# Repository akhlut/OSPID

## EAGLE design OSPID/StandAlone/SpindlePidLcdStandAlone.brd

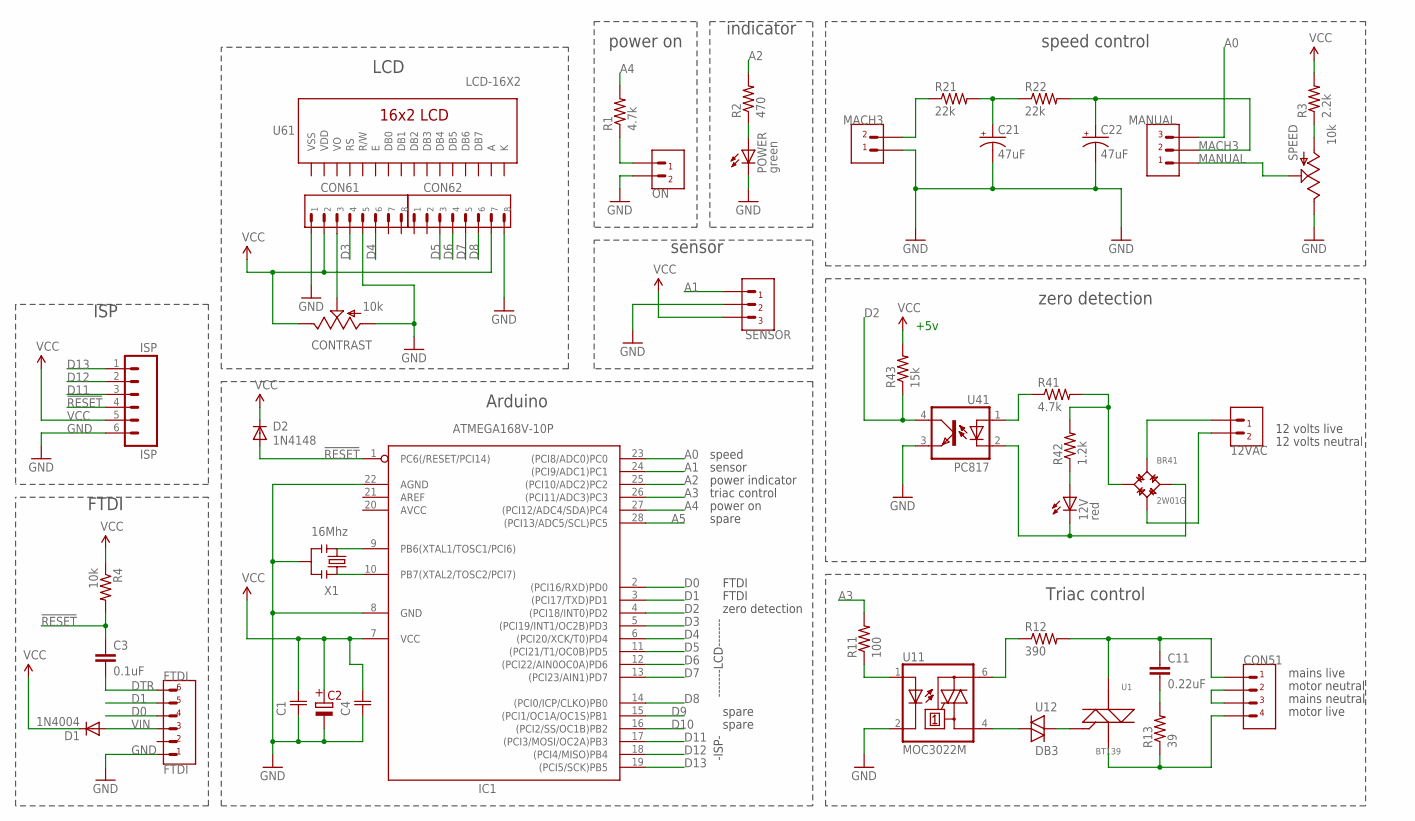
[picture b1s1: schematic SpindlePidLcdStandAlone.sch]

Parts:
12V: red; LED5MM
12VAC: 2PIN
BR41: 2W01G; DIODEBRIDGE
C1, C4: 0.1UF
C2: CAPACITOR
C3: 0.1uF; CAP-PTH-SMALL
C11: 0.22uF; CAP-PTH-SMALL
C21, C22: 47uF; CPOL-RADIAL-10UF-25V
CON51: 4PIN
CON61, CON62: 8PINHEADER
CONTRAST: 10k; ALPS_POT
D1: 1N4004; DO41-10
D2: 1N4148; DO41-10
FTDI: FTDI; 6PINHEADER
IC1: ATMEGA168V-10P; DIL28-3
ISP: ISP; 1X06
MACH3: 2PIN
MANUAL: 3PIN
ON: 2PIN
POWER: green; LED5MM
R1: 4.7k; AXIAL-0.4
R2: 470; 1/6W-RES
R3: 2.2k; 1/6W-RES
R4: 10k; AXIAL-0.4
R11: 100; 1/6W-RES
R12: 390; 1/6W-RES
R13: 39; 1/6W-RES
R21, R22: 22k; 1/6W-RES
R41: 4.7k; 1/6W-RES
R42: 1.2k; 1/6W-RES
R43: 15k; 1/6W-RES
SENSOR: 3PIN
SPEED: 10k; ALPS_POT
U1: BT139; TRIAC
U11: MOC3022M; DIL06
U12: DB3; DO35-10
U41: PC817; DIL04
U61: LCD-16X2
X1: 16Mhz; RESONATOR-PTH

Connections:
!RESET: C3.1, D2.A, IC1.1 (PC6(/RESET/PCI14)), ISP.4, R4.P$2 (2)
A: U61.15 (A)
A0: IC1.23 ((PCI8/ADC0)PC0), MANUAL.P$3 (3)
A1: IC1.24 ((PCI9/ADC1)PC1), SENSOR.P$1 (1)
A2: IC1.25 ((PCI10/ADC2)PC2), R2.2
A3: IC1.26 ((PCI11/ADC3)PC3), R11.2
A4: IC1.27 ((PCI12/ADC4/SDA)PC4), R1.P$2 (2)
A5: IC1.28 ((PCI13/ADC5/SCL)PC5)
D0: FTDI.P$4, IC1.2 ((PCI16/RXD)PD0)
D1: FTDI.P$5, IC1.3 ((PCI17/TXD)PD1)
D2: IC1.4 ((PCI18/INT0)PD2), R43.1, U41.4 (COL)
D3: CON61.P$4, IC1.5 ((PCI19/INT1/OC2B)PD3)
D4: CON61.P$6, IC1.6 ((PCI20/XCK/T0)PD4)
D5: CON62.P$3, IC1.11 ((PCI21/T1/OC0B)PD5)
D6: CON62.P$4, IC1.12 ((PCI22/AIN0OC0A)PD6)
D7: CON62.P$5, IC1.13 ((PCI23/AIN1)PD7)
D8: CON62.P$6, IC1.14 ((PCI0/ICP/CLKO)PB0)
D9: IC1.15 ((PCI1/OC1A/OC1S)PB1)
D10: IC1.16 ((PCI2/SS/OC1B)PB2)
D11: IC1.17 ((PCI3/MOSI/OC2A)PB3), ISP.3
D12: IC1.18 ((PCI4/MISO)PB4), ISP.2
D13: IC1.19 ((PCI5/SCK)PB5), ISP.1
DTR: C3.2, FTDI.P$6
GND: C1.P$1, C2.- (-VE), C4.P$1, C21.2 (-), C22.2 (-), CON61.P$1, CON61.P$5, CON62.P$8, CONTRAST.P$3 (A), FTDI.P$1, IC1.8 (GND), IC1.22 (AGND), ISP.6, MACH3.P$1, ON.P$2, POWER.K (C), SENSOR.P$2 (2), SPEED.P$1 (E), U11.2 (C), U41.3 (EMIT), X1.2
K: U61.16 (K)
MACH3: C22.1 (+), MANUAL.P$2 (2), R22.2
MACH3_PWM: MACH3.P$2, R21.1
MAINS_LIVE: C11.1, CON51.P$1, R12.2, U1.2 (A)
MANUAL: MANUAL.P$1 (1), SPEED.P$2 (S)
MOTOR_LIVE: CON51.P$4, R13.1, U1.3 (C)
unnamed: U1.1 (B), U12.C (2)
unnamed: C21.1 (+), R21.2, R22.1
unnamed: U11.4 (A1), U12.A (1)
unnamed: POWER.A, R2.1
unnamed: C11.2, R13.2
unnamed: 12V.A, R42.1
unnamed: R41.1, U41.1 (A)
unnamed: 12V.K (C), BR41.-, U41.2 (C)
unnamed: BR41.+, R41.2, R42.2
unnamed: R3.1, SPEED.P$3 (A)
unnamed: IC1.9 (PB6(XTAL1/TOSC1/PCI6)), X1.1
unnamed: ON.P$1, R1.P$1 (1)
unnamed: R11.1, U11.1 (A)
unnamed: 12VAC.P$1, BR41.AC1
unnamed: R12.1, U11.6 (A2)
unnamed: 12VAC.P$2, BR41.AC2
unnamed: CON61.P$3, CONTRAST.P$2 (S)
unnamed: IC1.10 (PB7(XTAL2/TOSC2/PCI7)), X1.3
NEUTRAL: CON51.P$2, CON51.P$3
VCC: C1.P$2, C2.+ (+VE), C4.P$2, CON61.P$2, CON62.P$7, CONTRAST.P$1 (E), D1.C, D2.C, IC1.7 (VCC), ISP.5, R3.2, R4.P$1 (1), R43.2, SENSOR.P$3 (3)
VDD: U61.2 (VDD)
VIN: D1.A, FTDI.P$3
VSS: U61.1 (VSS)

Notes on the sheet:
+5v
speed control
Arduino
sensor
power on
indicator
Triac control
zero detection
motor live
mains live
mains neutral
motor neutral
12 volts live
12 volts neutral
FTDI
ISP
LCD
-------LCD-------
-ISP-
speed
power indicator
triac control
spare

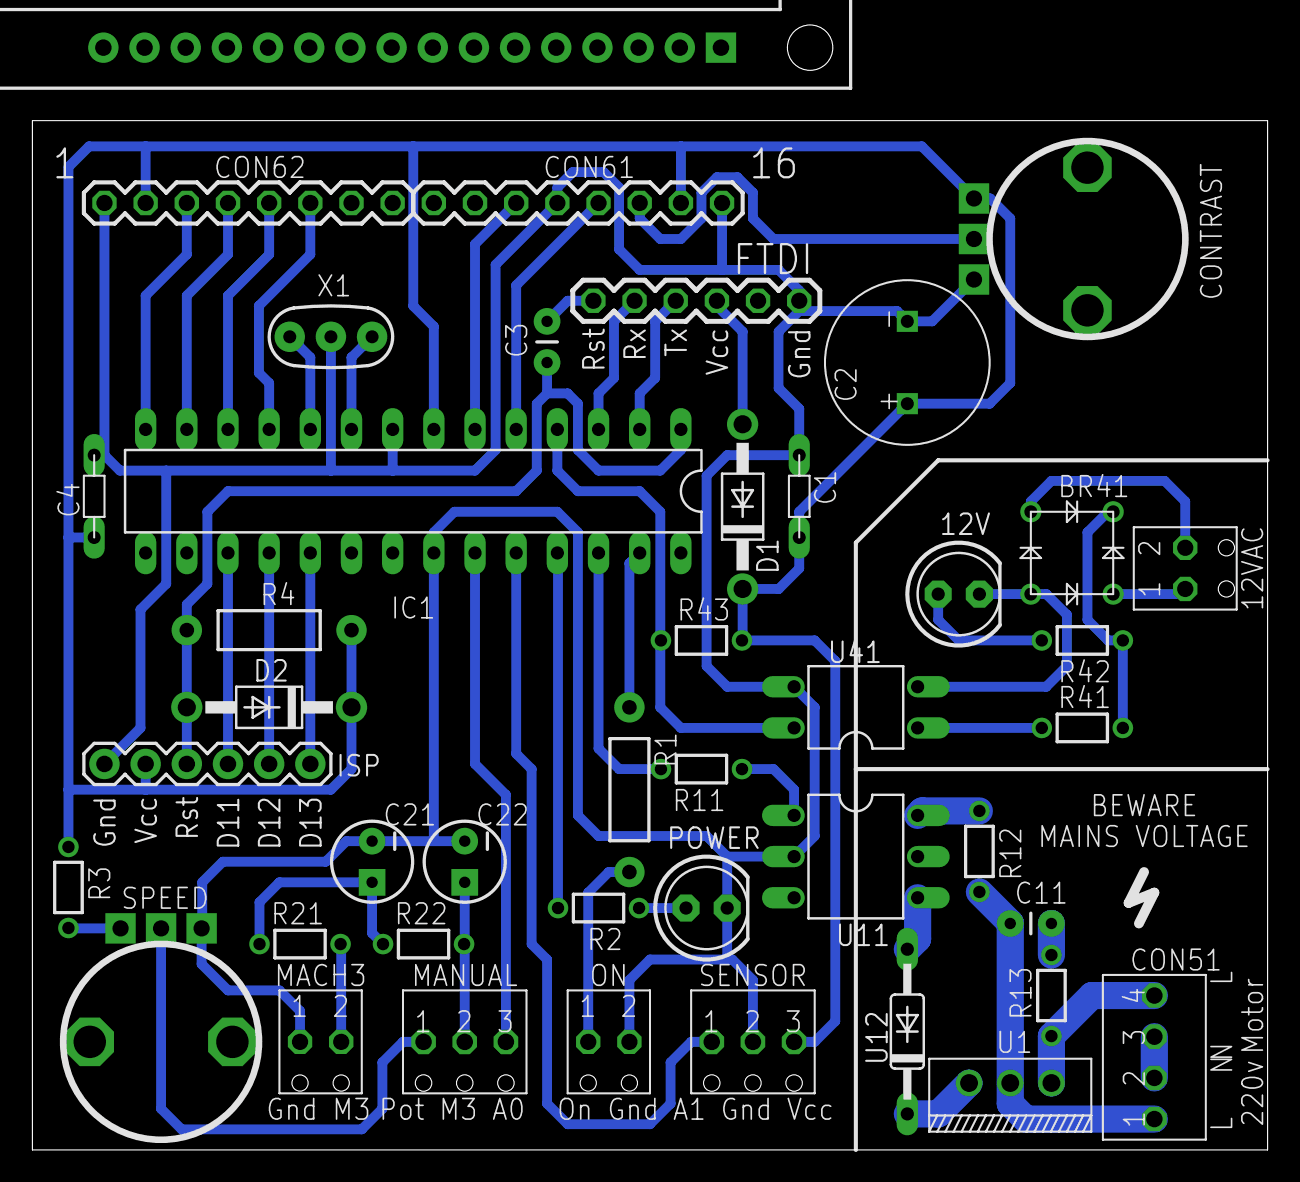
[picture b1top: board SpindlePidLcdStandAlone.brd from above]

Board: 2 copper layers, 76.2 x 63.5 mm, 43 parts (0 on the bottom side), 46 nets.

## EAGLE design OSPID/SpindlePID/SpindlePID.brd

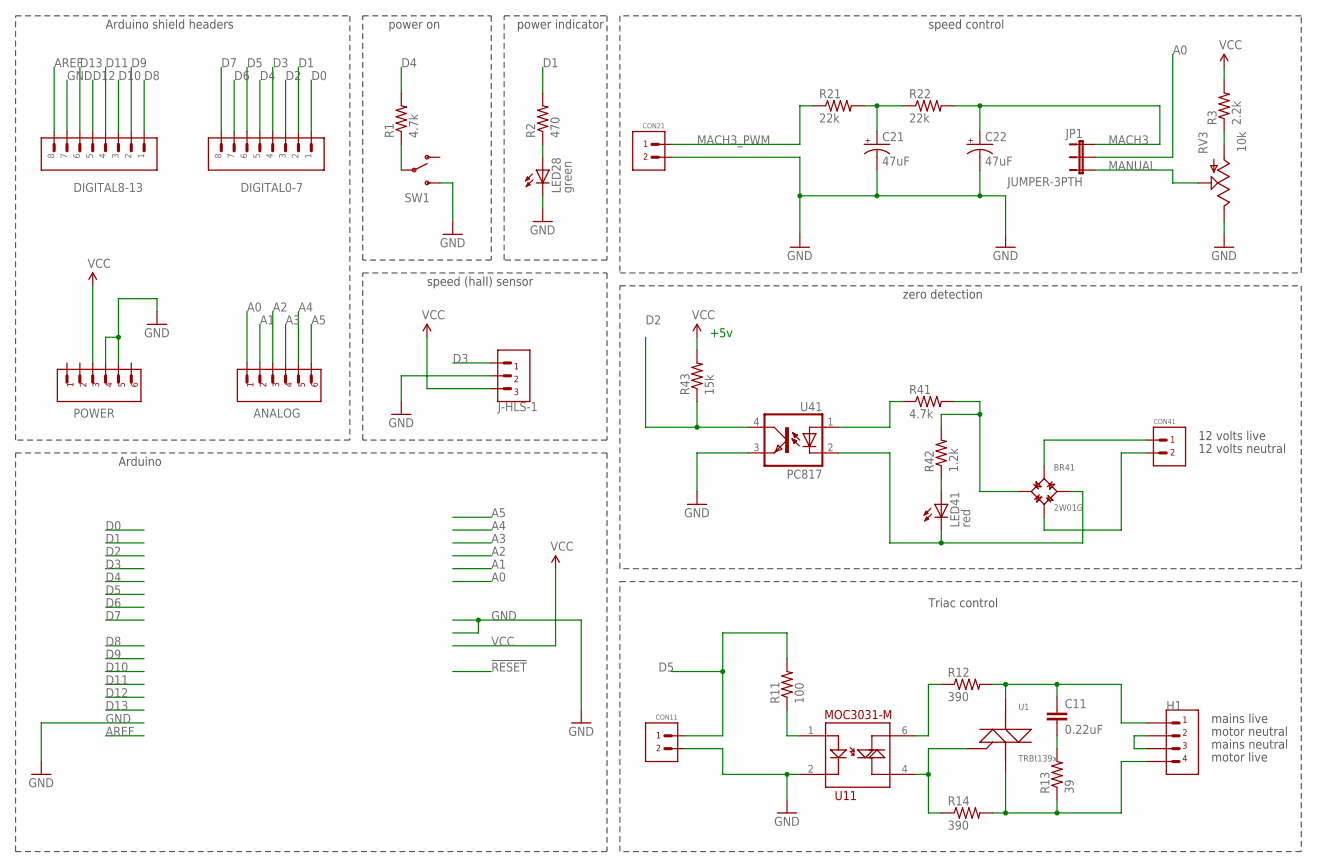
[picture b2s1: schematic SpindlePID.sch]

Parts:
ANALOG: 6PINHEADER0.1"; 6PINHEADER
BR41: 2W01G; DIODEBRIDGE
C11: 0.22uF; CAP-PTH-SMALL
C21, C22: 47uF; CPOL-RADIAL-10UF-25V
CON11, CON21, CON41: 2PINHEADER
DIGITAL0-7, DIGITAL8-13: 8PINHEADER
H1: 4PIN
J-HLS-1: 3PINHEADER
JP1: JUMPER-3PTH; 1X03
LED28: green; LED5MM
LED41: red; LED5MM
POWER: 6PINHEADER0.1"; 6PINHEADER
R1, R41: 4.7k; 1/6W-RES
R2: 470; 1/6W-RES
R3: 2.2k; 1/6W-RES
R11: 100; 1/6W-RES
R12, R14: 390; 1/6W-RES
R13: 39; 1/6W-RES
R21, R22: 22k; 1/6W-RES
R42: 1.2k; 1/6W-RES
R43: 15k; 1/6W-RES
RV3: 10k; TRIM_POT
SW1: SWITCH-SPSTPTH; SWITCH-SPDT
U1: TRBt139x; TRIAC
U11: MOC3031-M; DIL06
U41: PC817; DIL04

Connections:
A0: ANALOG.P$1, JP1.2
A1: ANALOG.P$2
A2: ANALOG.P$3
A3: ANALOG.P$4
A4: ANALOG.P$5
A5: ANALOG.P$6
AREF: DIGITAL8-13.P$8
D0: DIGITAL0-7.P$1
D1: DIGITAL0-7.P$2, R2.2
D2: DIGITAL0-7.P$3, R43.1, U41.4 (COL)
D3: DIGITAL0-7.P$4, J-HLS-1.P$3
D4: DIGITAL0-7.P$5, R1.2
D5: CON11.P$1, DIGITAL0-7.P$6, R11.2
D6: DIGITAL0-7.P$7
D7: DIGITAL0-7.P$8
D8: DIGITAL8-13.P$1
D9: DIGITAL8-13.P$2
D10: DIGITAL8-13.P$3
D11: DIGITAL8-13.P$4
D12: DIGITAL8-13.P$5
D13: DIGITAL8-13.P$6
GND: C21.2 (-), C22.2 (-), CON11.P$2, CON21.P$2, DIGITAL8-13.P$7, J-HLS-1.P$2, LED28.K (C), POWER.P$4, POWER.P$5, RV3.2 (E), SW1.3 (S), U11.2, U41.3 (EMIT)
MACH3: C22.1 (+), JP1.1, R22.2
MACH3_PWM: CON21.P$1, R21.1
MAINS_LIVE: C11.1, H1.P$1, R12.2, U1.2 (A)
MANUAL: JP1.3, RV3.1 (S)
MOTOR_LIVE: H1.P$4, R13.1, R14.2, U1.3 (C)
unnamed: C21.1 (+), R21.2, R22.1
unnamed: R14.1, U1.1 (B), U11.4
unnamed: LED28.A, R2.1
unnamed: C11.2, R13.2
unnamed: LED41.A, R42.1
unnamed: R41.1, U41.1 (A)
unnamed: BR41.-, LED41.K (C), U41.2 (C)
unnamed: BR41.+, R41.2, R42.2
unnamed: R3.1, RV3.3 (A)
unnamed: R1.1, SW1.2
unnamed: R11.1, U11.1
unnamed: BR41.AC1, CON41.P$1
unnamed: R12.1, U11.6
unnamed: BR41.AC2, CON41.P$2
NEUTRAL: H1.P$2, H1.P$3
VCC: J-HLS-1.P$1, POWER.P$3, R3.2, R43.2

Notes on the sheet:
+5v
speed control
Arduino shield headers
Arduino
speed (hall) sensor
power on
power indicator
Triac control
zero detection
motor live
mains live
mains neutral
motor neutral
12 volts live
12 volts neutral

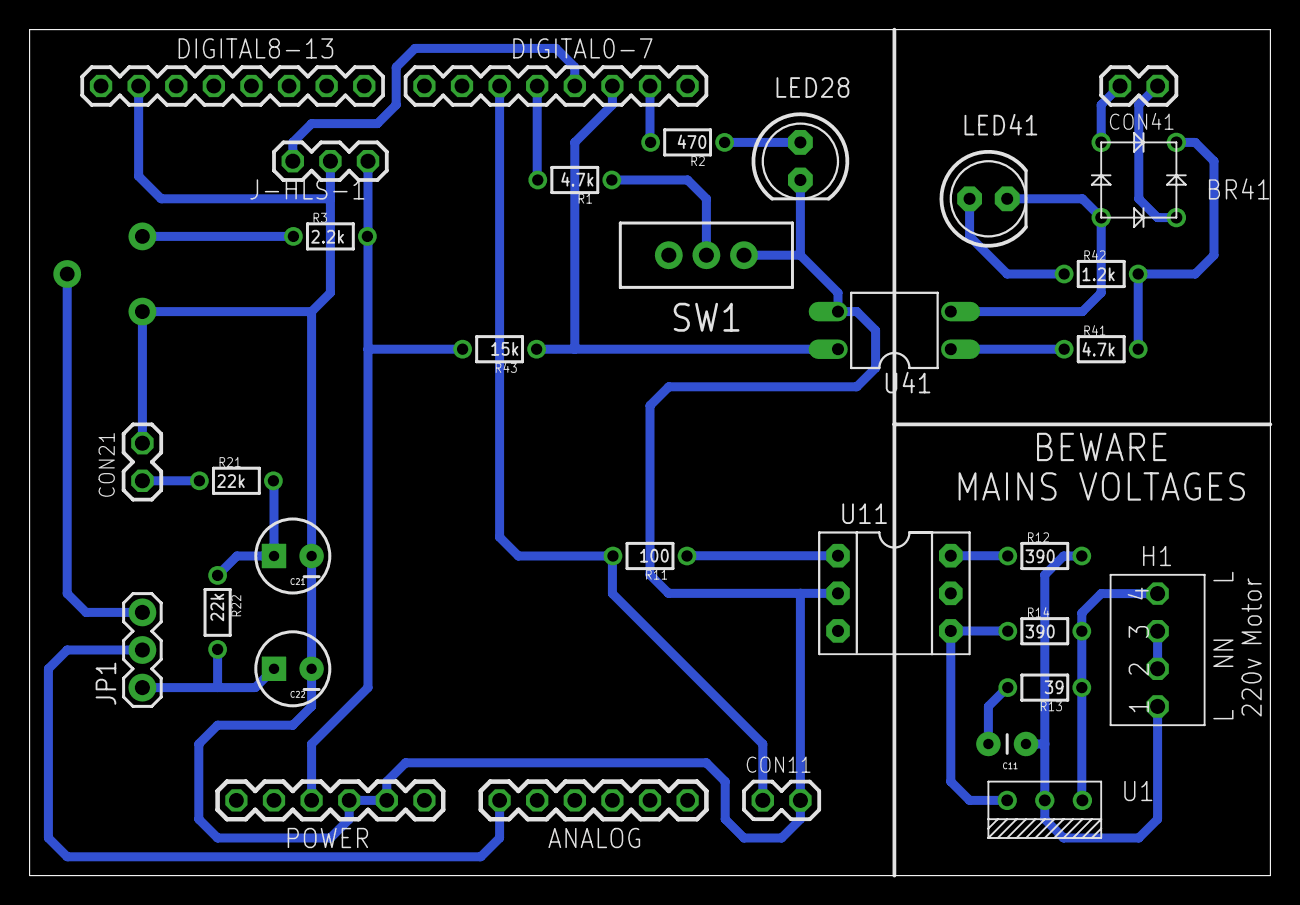
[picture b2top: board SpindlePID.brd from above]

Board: 2 copper layers, 83.8 x 57.1 mm, 33 parts (0 on the bottom side), 28 nets.

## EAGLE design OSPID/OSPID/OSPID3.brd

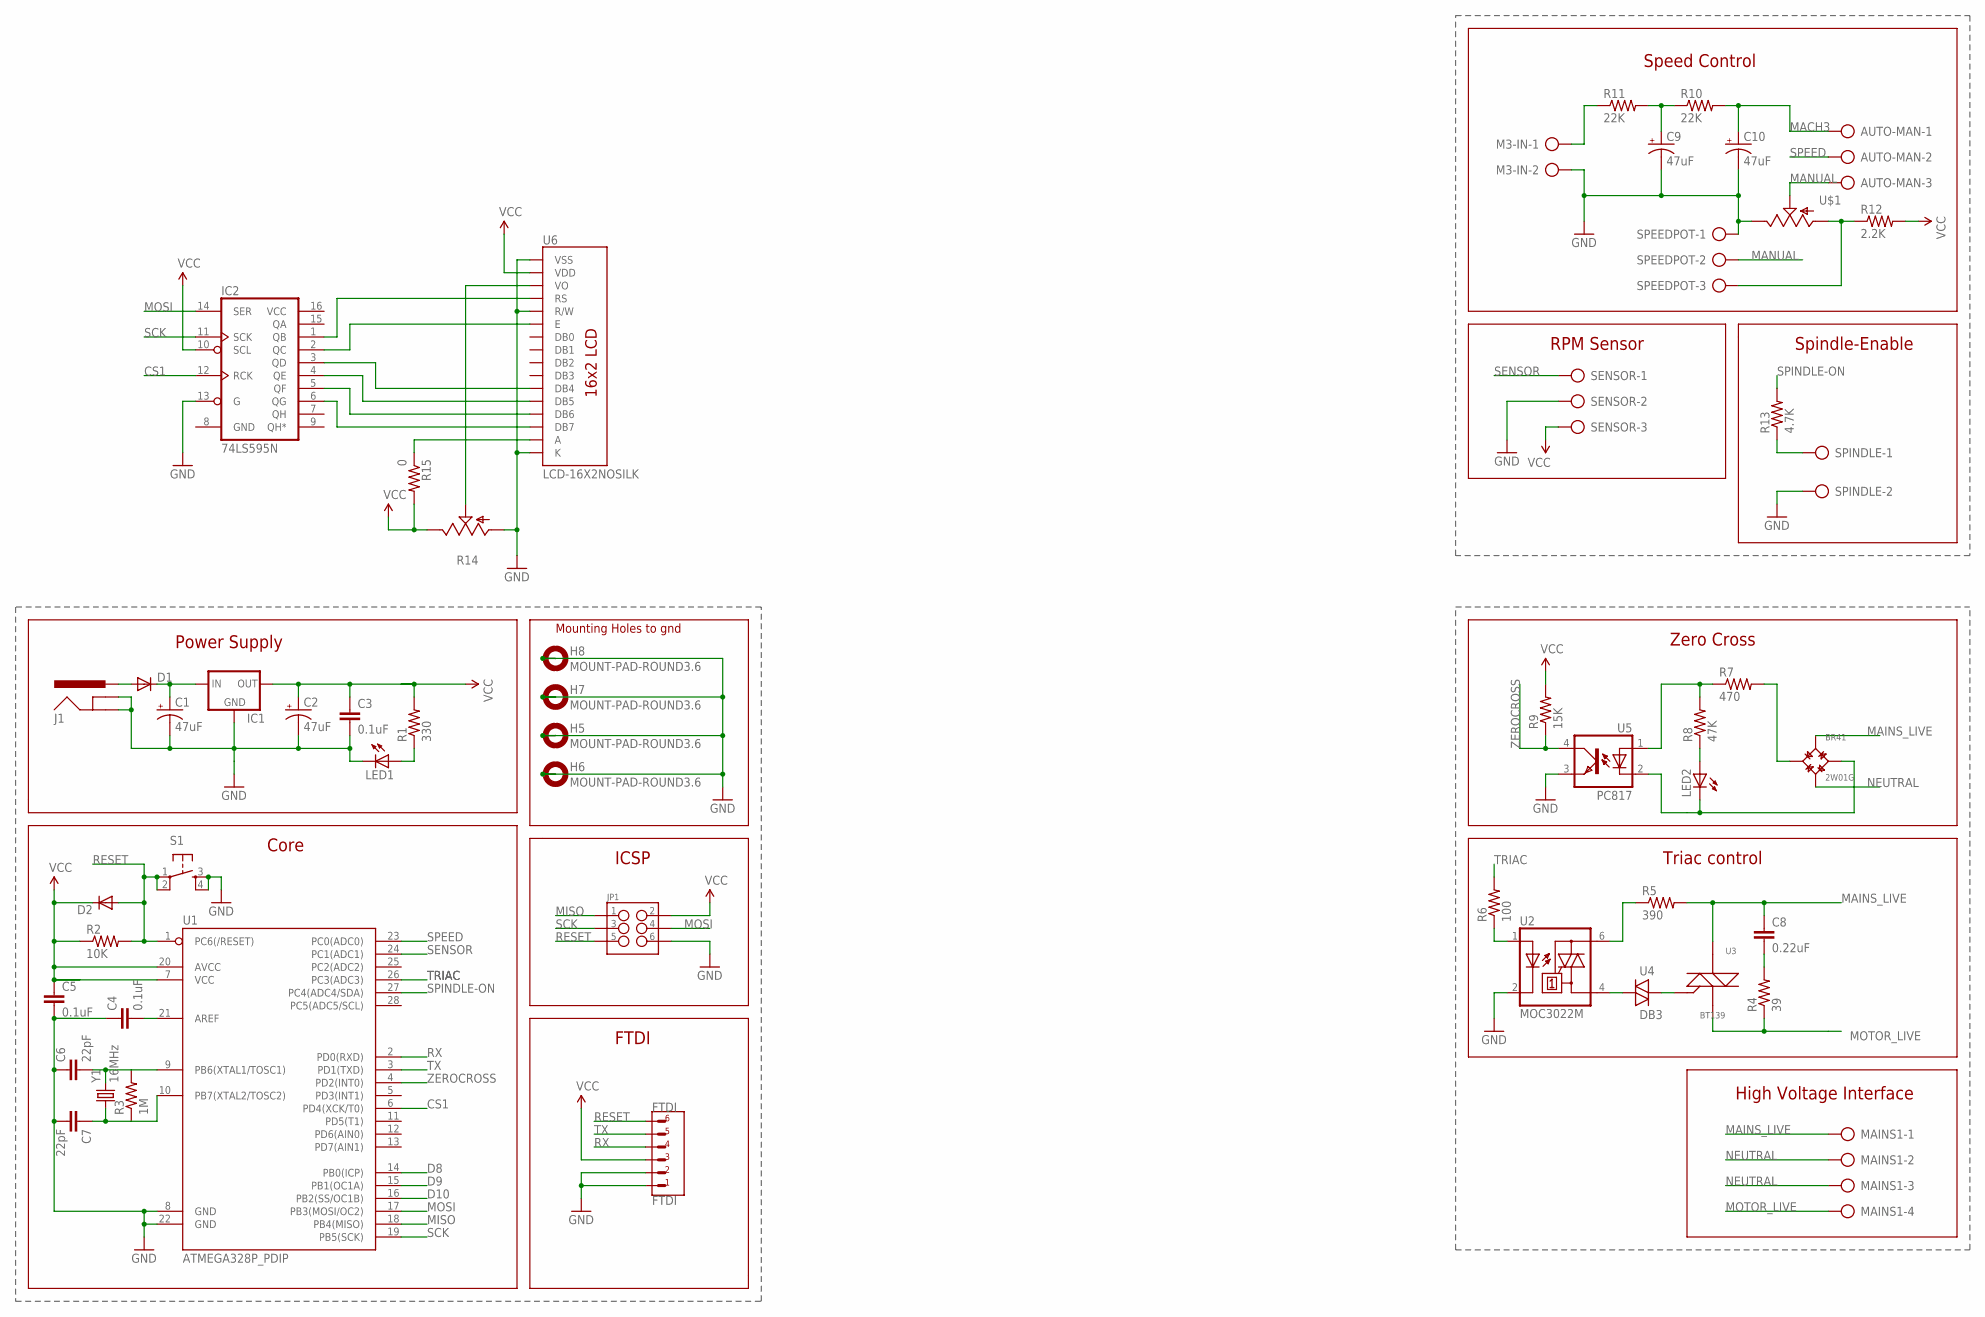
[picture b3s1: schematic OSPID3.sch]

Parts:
AUTO-MAN: AK500/3
BR41: 2W01G; DIODEBRIDGE
C1, C2, C9, C10: 47uF; CPOL-RADIAL-10UF-25V
C3, C4, C5: 0.1uF; CAP-PTH-SMALL
C6, C7: 22pF; CAP-PTH-SMALL
C8: 0.22uF; CAP-PTH-SMALL
D1, D2: DIODEPTH; DIODE-1N4001
FTDI: FTDI; 6PINHEADER
H5, H6, H7, H8: MOUNT-PAD-ROUND3.6; 3,6-PAD
IC1: V_REG_78XX-TO-220; TO-220-ALT
IC2: 74LS595N; DIL16
J1: POWER_JACKPTH_LOCK; POWER_JACK_PTH_LOCK
JP1: M03X2POGO_PINS; 2X3_POGO
LED1, LED2: LED5MM
M3-IN: AK500/2
MAINS1: AK500/4
R1: 330; AXIAL-0.3
R2: 10K; AXIAL-0.3
R3: 1M; AXIAL-0.3
R4: 39; AXIAL-0.3
R5: 390; AXIAL-0.3
R6: 100; AXIAL-0.3
R7: 470; SQM_5-10
R8: 47K; SQM_5-10
R9: 15K; AXIAL-0.3
R10, R11: 22K; AXIAL-0.3
R12: 2.2K; AXIAL-0.3
R13: 4.7K; AXIAL-0.3
R14: POT_TRIM_US-B25U; POT_B25U
R15: 0; AXIAL-0.3
S1: TAC_SWITCHPTH; TACTILE-PTH
SENSOR: AK500/3
SPEEDPOT: AK500/3
SPINDLE: AK500/2
U1: ATMEGA328P_PDIP; DIL28-3
U2: MOC3022M; DIL06
U3: BT139; TRIAC
U4: DB3; DO35-10
U5: PC817; DIL04
U6: LCD-16X2NOSILK; LCD-16X2_NOSILK
U$1: POT; ALPS_POT
Y1: 16MHz; HC49U-V

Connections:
CS1: IC2.12 (RCK), U1.6 (PD4(XCK/T0))
D8: U1.14 (PB0(ICP))
D9: U1.15 (PB1(OC1A))
D10: U1.16 (PB2(SS/OC1B))
GND: C1.2 (-), C2.2 (-), C3.2, C4.1, C5.2, C6.1, C7.2, C9.2 (-), C10.2 (-), FTDI.P$1, FTDI.P$2, H5.B3,6, H6.B3,6, H7.B3,6, H8.B3,6, IC1.GND, IC2.8 (GND), IC2.13 (G), J1.GND, J1.GNDBREAK, JP1.P$6 (6), LED1.K (C), M3-IN.2, R14.A, S1.3, S1.4, SENSOR.2, SPEEDPOT.1, SPINDLE.2, U1.8 (GND), U1.22 (GND), U2.2 (C), U5.3 (EMIT), U6.1 (VSS), U6.5 (R/W), U6.16 (K), U$1.P$1 (E)
MACH3: AUTO-MAN.1, C10.1 (+), R10.P$2 (2)
MACH3_PWM: M3-IN.1, R11.P$1 (1)
MAINS_LIVE: BR41.AC1, C8.1, MAINS1.1, R5.P$2 (2), U3.2 (A)
MANUAL: AUTO-MAN.3, SPEEDPOT.2, U$1.P$2 (S)
MISO: JP1.P$1 (1), U1.18 (PB4(MISO))
MOSI: IC2.14 (SER), JP1.P$4 (4), U1.17 (PB3(MOSI/OC2))
MOTOR_LIVE: MAINS1.4, R4.P$1 (1), U3.3 (C)
unnamed: U3.1 (B), U4.C (2)
unnamed: C9.1 (+), R10.P$1 (1), R11.P$2 (2)
unnamed: U2.4 (A1), U4.A (1)
unnamed: LED1.A, R1.P$1 (1)
unnamed: C8.2, R4.P$2 (2)
unnamed: R7.P1 (1), R8.P2 (2), U5.1 (A)
unnamed: BR41.-, LED2.K (C), U5.2 (C)
unnamed: LED2.A, R8.P1 (1)
unnamed: R12.P$1 (1), SPEEDPOT.3, U$1.P$3 (A)
unnamed: R13.P$1 (1), SPINDLE.1
unnamed: R6.P$1 (1), U2.1 (A)
unnamed: R14.S, U6.3 (VO)
unnamed: R5.P$1 (1), U2.6 (A2)
unnamed: R15.P$1 (1), U6.15 (A)
unnamed: IC2.1 (QB), U6.4 (RS)
unnamed: IC2.2 (QC), U6.6 (E)
unnamed: C7.1, R3.P$1 (1), U1.10 (PB7(XTAL2/TOSC2)), Y1.1
unnamed: IC2.6 (QG), U6.14 (DB7)
unnamed: C6.2, R3.P$2 (2), U1.9 (PB6(XTAL1/TOSC1)), Y1.2
unnamed: IC2.5 (QF), U6.13 (DB6)
unnamed: IC2.4 (QE), U6.12 (DB5)
unnamed: C1.1 (+), D1.C, IC1.IN
unnamed: D1.A, J1.PWR
unnamed: IC2.3 (QD), U6.11 (DB4)
unnamed: C4.2, U1.21 (AREF)
unnamed: BR41.+, R7.P2 (2)
NEUTRAL: BR41.AC2, MAINS1.2, MAINS1.3
RESET: D2.A, FTDI.P$6, JP1.P$5 (5), R2.P$2 (2), S1.1, S1.2, U1.1 (PC6(/RESET))
RX: FTDI.P$4, U1.2 (PD0(RXD))
SCK: IC2.11 (SCK), JP1.P$3 (3), U1.19 (PB5(SCK))
SENSOR: SENSOR.1, U1.24 (PC1(ADC1))
SPEED: AUTO-MAN.2, U1.23 (PC0(ADC0))
SPINDLE-ON: R13.P$2 (2), U1.27 (PC4(ADC4/SDA))
TRIAC: R6.P$2 (2), U1.26 (PC3(ADC3))
TX: FTDI.P$5, U1.3 (PD1(TXD))
VCC: C2.1 (+), C3.1, C5.1, D2.C, FTDI.P$3, IC1.OUT, IC2.10 (SCL), IC2.16 (VCC), JP1.P$2 (2), R1.P$2 (2), R2.P$1 (1), R9.P$2 (2), R12.P$2 (2), R14.E, R15.P$2 (2), SENSOR.3, U1.7 (VCC), U1.20 (AVCC), U6.2 (VDD)
ZEROCROSS: R9.P$1 (1), U1.4 (PD2(INT0)), U5.4 (COL)

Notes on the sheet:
Speed Control
RPM Sensor
Spindle-Enable
Power Supply
Triac control
Zero Cross
FTDI
Core
ICSP
High Voltage Interface
Mounting Holes to gnd

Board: 2 copper layers, 54 parts (0 on the bottom side), 46 nets, no tracks yet.

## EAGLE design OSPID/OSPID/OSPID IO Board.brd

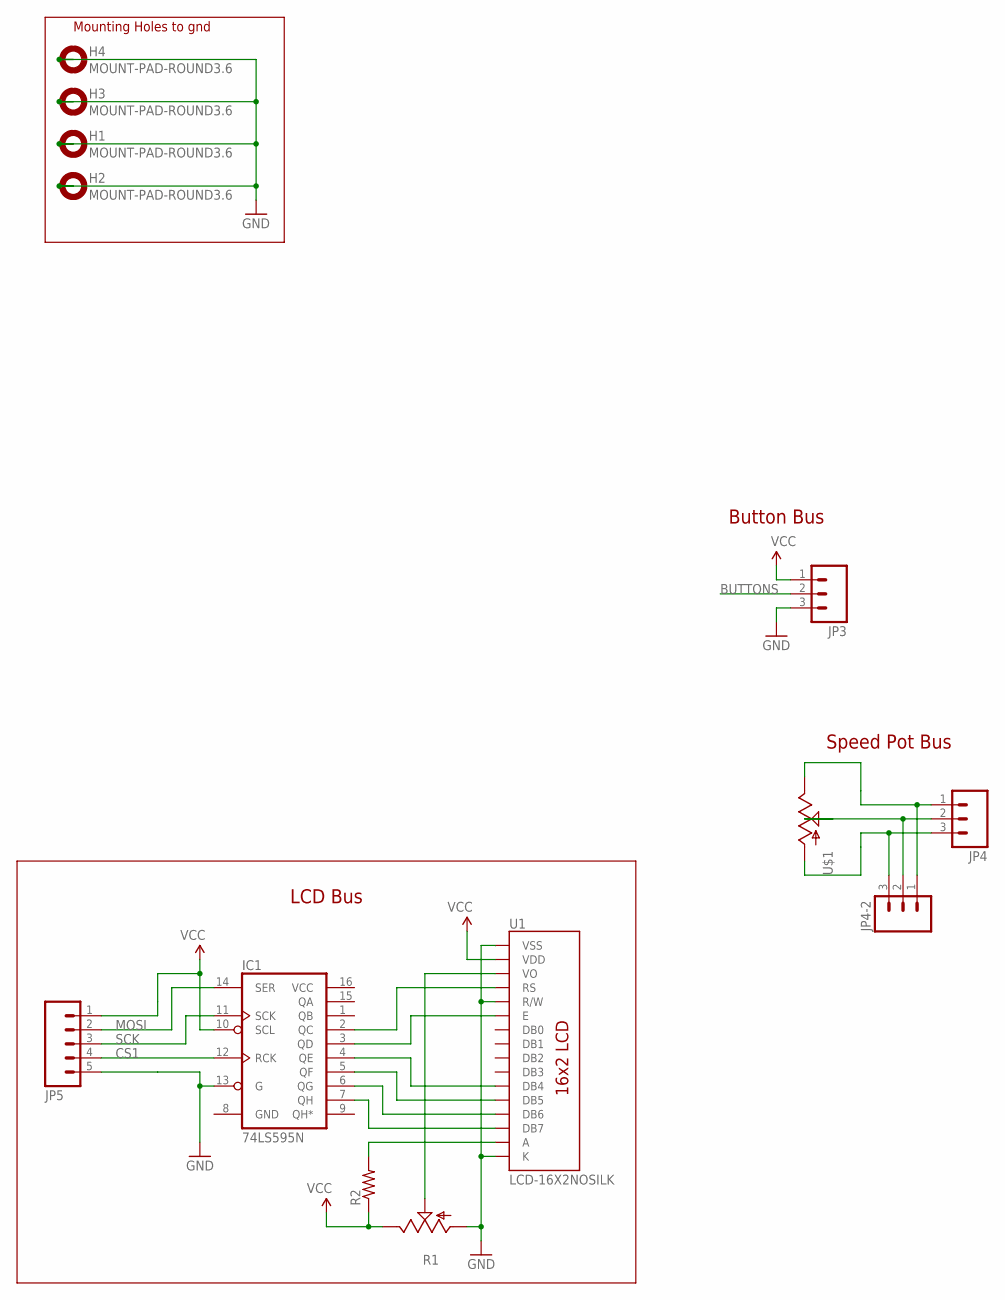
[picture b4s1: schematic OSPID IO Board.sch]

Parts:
H1, H2, H3, H4: MOUNT-PAD-ROUND3.6; 3,6-PAD
IC1: 74LS595N; DIL16
JP3, JP4, JP4-2: M03LOCK; 1X03_LOCK
JP5: M05LOCK; 1X05_LOCK
R1: POT_TRIM_US-B25U; POT_B25U
R2: RESISTORAXIAL-0.3; AXIAL-0.3
U1: LCD-16X2NOSILK; LCD-16X2_NOSILK
U$1: POT; ALPS_POT

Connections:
BUTTONS: JP3.2
CS1: IC1.12 (RCK), JP5.4
GND: H1.B3,6, H2.B3,6, H3.B3,6, H4.B3,6, IC1.8 (GND), IC1.13 (G), JP3.3, JP5.5, R1.A, U1.1 (VSS), U1.5 (R/W), U1.16 (K)
MOSI: IC1.14 (SER), JP5.2
unnamed: JP4.3, JP4-2.3, U$1.P$3 (A)
unnamed: R2.P$2 (2), U1.15 (A)
unnamed: JP4.2, JP4-2.2, U$1.P$2 (S)
unnamed: JP4.1, JP4-2.1, U$1.P$1 (E)
unnamed: IC1.4 (QE), U1.11 (DB4)
unnamed: IC1.2 (QC), U1.4 (RS)
unnamed: IC1.3 (QD), U1.6 (E)
unnamed: R1.S, U1.3 (VO)
unnamed: IC1.5 (QF), U1.12 (DB5)
unnamed: IC1.6 (QG), U1.13 (DB6)
unnamed: IC1.7 (QH), U1.14 (DB7)
SCK: IC1.11 (SCK), JP5.3
VCC: IC1.10 (SCL), IC1.16 (VCC), JP3.1, JP5.1, R1.E, R2.P$1 (1), U1.2 (VDD)

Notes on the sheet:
Button Bus
LCD Bus
Mounting Holes to gnd
Speed Pot Bus

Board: 2 copper layers, 13 parts (0 on the bottom side), 16 nets, no tracks yet.

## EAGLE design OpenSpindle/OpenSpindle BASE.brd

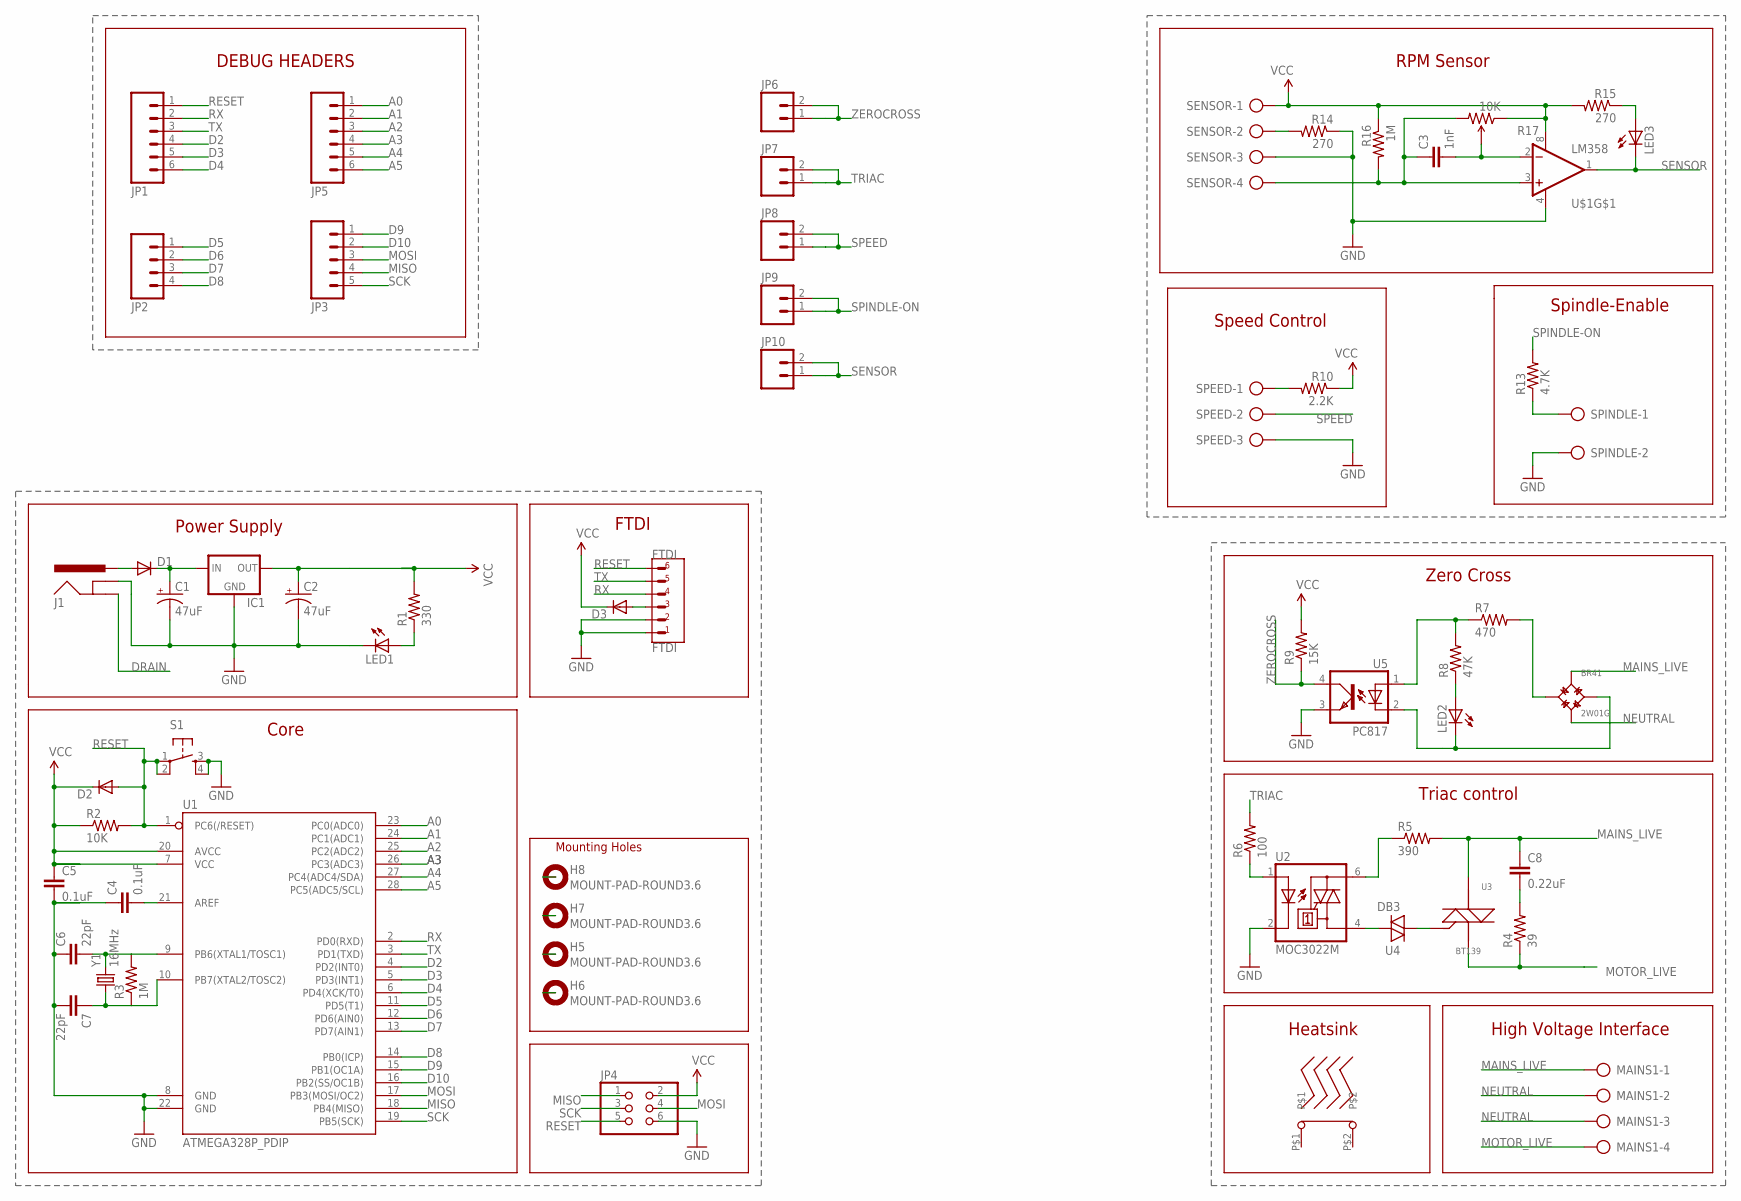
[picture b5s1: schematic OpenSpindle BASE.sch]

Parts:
BR41: 2W01G; DIODEBRIDGE
C1, C2: 47uF; CPOL-RADIAL-10UF-25V
C3: 1nF; CAP-PTH-SMALL
C4, C5: 0.1uF; CAP-PTH-SMALL
C6, C7: 22pF; CAP-PTH-SMALL
C8: 0.22uF; CAP-PTH-SMALL
D1, D2, D3: DIODEPTH; DIODE-1N4001
FTDI: FTDI; 6PINHEADER
H5, H6, H7, H8: MOUNT-PAD-ROUND3.6; 3,6-PAD
IC1: V_REG_78XX-TO-220; TO-220-ALT
J1: POWER_JACKPTH_LOCK; POWER_JACK_PTH_LOCK
JP1, JP5: M06LOCK; 1X06_LOCK
JP2: M04LOCK; 1X04_LOCK
JP3: M05LOCK; 1X05_LOCK
JP4: PINHD-2X3; 2X03
JP6, JP7, JP8, JP9, JP10: M02LOCK; 1X02_LOCK
LED1, LED2, LED3: LED5MM
MAINS1: AK500/4
R1: 330; AXIAL-0.3
R2: 10K; AXIAL-0.3
R3, R16: 1M; AXIAL-0.3
R4: 39; AXIAL-0.3
R5: 390; AXIAL-0.3
R6: 100; AXIAL-0.3
R7: 470; SQM_5-10
R8: 47K; SQM_5-10
R9: 15K; AXIAL-0.3
R10: 2.2K; AXIAL-0.3
R13: 4.7K; AXIAL-0.3
R14, R15: 270; AXIAL-0.3
R17: 10K; TRIMPOT_PTH_S3_LOCK
S1: TAC_SWITCHPTH; TACTILE-PTH
SENSOR: AK500/4
SPEED: AK500/3
SPINDLE: AK500/2
U1: ATMEGA328P_PDIP; DIL28-3
U2: MOC3022M; DIL06
U3: BT139; TRIAC
U4: DB3; DO35-10
U5: PC817; DIL04
U$1: LM358; DIP08
U$2: HEATSINK529802B02500G; 529802B02500G
Y1: 16MHz; HC49U-V

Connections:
A0: JP5.1, U1.23 (PC0(ADC0))
A1: JP5.2, U1.24 (PC1(ADC1))
A2: JP5.3, U1.25 (PC2(ADC2))
A3: JP5.4, U1.26 (PC3(ADC3))
A4: JP5.5, U1.27 (PC4(ADC4/SDA))
A5: JP5.6, U1.28 (PC5(ADC5/SCL))
D2: JP1.4, U1.4 (PD2(INT0))
D3: JP1.5, U1.5 (PD3(INT1))
D4: JP1.6, U1.6 (PD4(XCK/T0))
D5: JP2.1, U1.11 (PD5(T1))
D6: JP2.2, U1.12 (PD6(AIN0))
D7: JP2.3, U1.13 (PD7(AIN1))
D8: JP2.4, U1.14 (PB0(ICP))
D9: JP3.1, U1.15 (PB1(OC1A))
D10: JP3.2, U1.16 (PB2(SS/OC1B))
DRAIN: J1.GND
GND: C1.2 (-), C2.2 (-), C4.1, C5.2, C6.1, C7.2, FTDI.P$1, FTDI.P$2, IC1.GND, J1.GNDBREAK, JP4.6, LED1.K (C), R14.P$1 (1), S1.3, S1.4, SENSOR.3, SPEED.3, SPINDLE.2, U1.8 (GND), U1.22 (GND), U2.2 (C), U5.3 (EMIT), U$1.4 (V-)
MAINS_LIVE: BR41.AC1, C8.1, MAINS1.1, R5.P$2 (2), U3.2 (A)
MISO: JP3.4, JP4.1, U1.18 (PB4(MISO))
MOSI: JP3.3, JP4.4, U1.17 (PB3(MOSI/OC2))
MOTOR_LIVE: MAINS1.4, R4.P$1 (1), U3.3 (C)
unnamed: U2.4 (A1), U4.C (2)
unnamed: R10.P$2 (2), SPEED.1
unnamed: U3.1 (B), U4.A (1)
unnamed: LED1.A, R1.P$1 (1)
unnamed: C8.2, R4.P$2 (2)
unnamed: R7.P1 (1), R8.P2 (2), U5.1 (A)
unnamed: BR41.-, LED2.K (C), U5.2 (C)
unnamed: LED2.A, R8.P1 (1)
unnamed: R13.P$1 (1), SPINDLE.1
unnamed: R6.P$1 (1), U2.1 (A)
unnamed: D3.A, FTDI.P$3
unnamed: R5.P$1 (1), U2.6 (A2)
unnamed: R14.P$2 (2), SENSOR.2
unnamed: C3.1, R16.P$2 (2), R17.3 (CW), SENSOR.4, U$1.3 (+IN)
unnamed: C7.1, R3.P$1 (1), U1.10 (PB7(XTAL2/TOSC2)), Y1.1
unnamed: C6.2, R3.P$2 (2), U1.9 (PB6(XTAL1/TOSC1)), Y1.2
unnamed: LED3.A, R15.P$1 (1)
unnamed: C1.1 (+), D1.C, IC1.IN
unnamed: D1.A, J1.PWR
unnamed: C3.2, R17.2 (WIPER), U$1.2 (-IN)
unnamed: C4.2, U1.21 (AREF)
unnamed: BR41.+, R7.P2 (2)
NEUTRAL: BR41.AC2, MAINS1.2, MAINS1.3
RESET: D2.A, FTDI.P$6, JP1.1, JP4.5, R2.P$2 (2), S1.1, S1.2, U1.1 (PC6(/RESET))
RX: FTDI.P$4, JP1.2, U1.2 (PD0(RXD))
SCK: JP3.5, JP4.3, U1.19 (PB5(SCK))
SENSOR: JP10.1, JP10.2, LED3.K (C), U$1.1 (OUT)
SPEED: JP8.1, JP8.2, SPEED.2
SPINDLE-ON: JP9.1, JP9.2, R13.P$2 (2)
TRIAC: JP7.1, JP7.2, R6.P$2 (2)
TX: FTDI.P$5, JP1.3, U1.3 (PD1(TXD))
VCC: C2.1 (+), C5.1, D2.C, D3.C, IC1.OUT, JP4.2, R1.P$2 (2), R2.P$1 (1), R9.P$2 (2), R10.P$1 (1), R15.P$2 (2), R16.P$1 (1), R17.1 (CCW), SENSOR.1, U1.7 (VCC), U1.20 (AVCC), U$1.8 (V+)
ZEROCROSS: JP6.1, JP6.2, R9.P$1 (1), U5.4 (COL)

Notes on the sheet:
Speed Control
RPM Sensor
Spindle-Enable
Power Supply
Triac control
Zero Cross
FTDI
Core
High Voltage Interface
Mounting Holes
Heatsink
DEBUG HEADERS

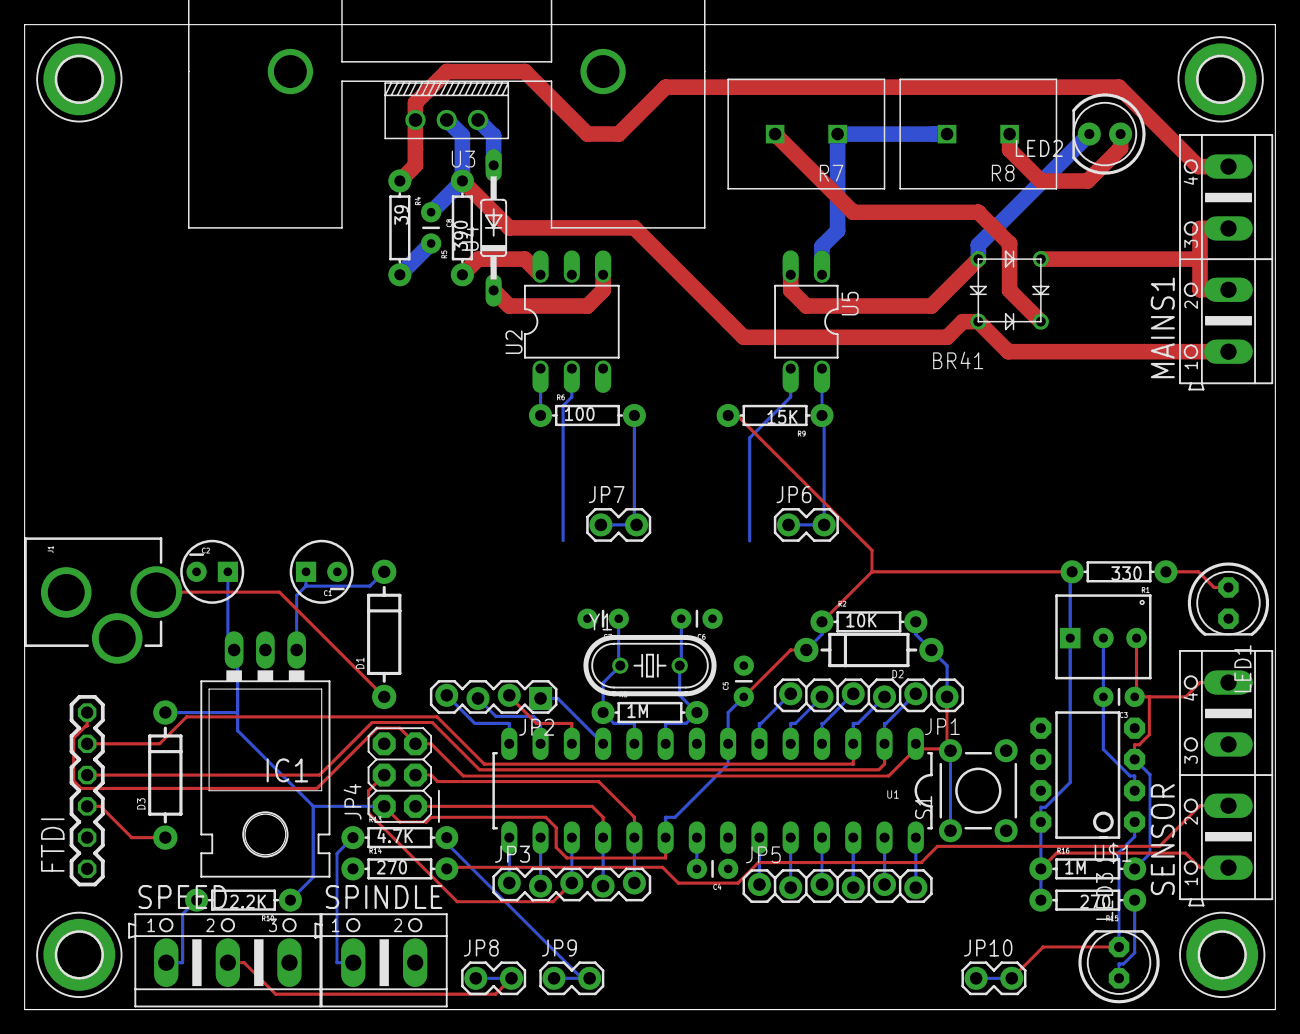
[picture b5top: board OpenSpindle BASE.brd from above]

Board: 2 copper layers, 101.6 x 80.0 mm, 60 parts (0 on the bottom side), 53 nets.

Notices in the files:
parts and their libraries:
SparkFun-Connectors: Licensing: CC v3.0 Share-Alike You are welcome to use this library for commercial purposes.
